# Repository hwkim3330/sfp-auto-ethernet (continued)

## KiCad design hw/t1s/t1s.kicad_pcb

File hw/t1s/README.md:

# T1S SFP: 10BASE-T1S

No 10BASE-T1S PHY speaks SGMII (they are all MII/RMII or SPI MAC-PHYs; see [../../docs/PARTS.md](../../docs/PARTS.md)).
So an FPGA sits between the two:
- the host's SGMII on a hard transceiver lane;
- our own PCS, ×100 rate adaptation, frame FIFOs and half-duplex MAC in fabric ([gw/](gw/));
- MII to a Microchip LAN8670.

**This is the board with the most unverified pieces.** See [What is not verified](#what-is-not-verified).

Schematic, 6-layer PCB (routed), fab outputs and a JLC panel are in place; the order sheet is [ORDER.md](ORDER.md). Nothing has been built.

**Re-laid 2026-10-08 on the corrected SFP edge** (SFF-8419 figure 7-2; until then the fingers were drawn mirrored, which would have put VccT on a ground contact). Do not order before the Gowin transceiver IP, synthesis and timing exist (below).

| Top | Bottom |
|---|---|
|  |  |

## Status

| | Result | How it was checked |
|---|---|---|
| Schematic | **ERC 0 errors** ([erc.rpt](erc.rpt)); 2 warnings, both "symbol differs from the library copy" (the two LDOs) | eeschema's own ERC (`run_erc.sh`) |
| Placement | 92 parts, no overlaps; housing height limits met | `make_t1s.py` |
| SFP edge | **all 20 fingers where SFF-8419 figure 7-2 puts them, with the right nets** | `tools/compliance.py` (positions written out independently of the generator) |
| Routing | **DRC 0 violations, 0 unconnected** ([drc.rpt](drc.rpt)) | hand-laid pairs, escapes and In2 buses, Freerouting 1.9.0 for the rest ([t1s.ses](t1s.ses), rebuilt with `--reuse-ses`), then KiCad DRC |
| KiCad 9 | **DRC 0 errors, 0 unconnected, schematic parity clean, ERC 0 errors** ([kicad9-drc.rpt](kicad9-drc.rpt), [kicad9-erc.rpt](kicad9-erc.rpt)) | `sh ../check_kicad9.sh t1s`. Only warnings are "differs from the library copy" |
| Fab | Gerbers + drill ([fab/t1s-gerbers.zip](fab/t1s-gerbers.zip)), [BOM](fab/t1s-bom.csv), [CPL](fab/t1s-cpl.csv), [1:1 print](fab/t1s-1to1.pdf) | `export_t1s.py` |
| Panel | 5 boards, 70.1 × 81.1 mm, **DRC 0 errors, 0 unconnected** with the board's rules ([jlc/panel-drc.rpt](jlc/panel-drc.rpt)) | `panel_t1s.py` (KiKit) |
| Gateware | `tb_bridge`, `tb_top` pass (`tb_top` with both lanes straight; an RX-inverting instance must fail) | Icarus Verilog, CI |
| Firmware | builds, 0 warnings | `make VARIANT=t1s`, CI |

## Parts

| | Part | LCSC | Why |
|---|---|---|---|
| FPGA | Gowin **GW5AT-LV15MG132C1/I0** | C54067362 | The only FPGA with real transceivers that fits the width (8 × 8 mm) and is in JLC stock |
| PHY | Microchip **LAN8670C2-E/LMX** | C20901523 | MII + PLCA, 5 × 5 VQFN (B1/C1 variants have no stock) |
| Reference | YXC OB2EL89CLIB112YLC-125M, 125 MHz LVDS 3225 | C7425465 | As the Gowin kit: LVDS, AC coupled at the FPGA |
| Configuration | GD25Q128EWIGR, 128 Mbit SPI NOR, WSON-8 6 × 5 | C2982923 | 128 Mbit so Gowin's default golden (retry) address 0x800000 is inside the part: main image at 0x000000, golden at 0x800000 |
| Core 0.946 V | TPS62822 buck | C473385 | Same circuit as the RJ45 board (57.6k / 100k) |
| 1.8 V, 1.2 V | TLV75518 / TLV75512, SOT-23-5 | C2877863 / C2877864 | VDDHAQ0; VDD12M + VCCLDO |
| MDI | ACT1210E-241 CMC, 2 × 100 nF 100 V, 49.9 Ω end-node termination | C6114822 … | Microchip AN1718 "BIN" |
| Connector | JST PH S2B-PH-K-S, 2 pins, right angle | C173752 | Wire to board, outside the cage |
| MCU | STM32G031F6P6 | C529333 | As the other boards: EEPROM, PHY bridge, TX_DISABLE / RX_LOS |

## Board

- 58.4 × 11.8 mm. The JST housing sits entirely past the cage front (44.3 mm).
- **Six layers:**

  | Layer | Use |
  |---|---|
  | F | FPGA balls, SGMII RX and the reference clock, MII, the beads, the MDI network, JTAG pads |
  | In1 | GND |
  | In2 | signals: the long buses (below), the ball field's escapes |
  | In3 | +3V3 plane |
  | In4 | GND, with the 0.95 V core as an island under the FPGA and the buck |
  | B | the TX pair, decaps, load switch, flash, buck, PHY straps, MCU, LDOs, test pads |

- **Why six:** 0.5 mm ball pitch leaves no room for a track between balls. So every used ball inside the outer ring has a **via in its pad** (0.25 / 0.15 mm in Gowin's 0.25 mm land, UG983 figure 4-8; filled and capped), and five supply rails sit interleaved around the ring. On six layers JLC fills and caps via-in-pad at no extra charge, and +3V3 and the core rail become planes the router doesn't have to route.
- **The core island is on In4, not In2.** On In2 it covered the ball field, so the small rails (VDDHAQ, V1P2) and the inner-ring signals had no way out. Under B only the field's stubs and decaps sit on it; the TX pair crosses it only on its last 0.75 mm into the balls.
- **Two In2 buses, laid by hand** (`IN2_BUS` in `make_t1s.py`; the long runs were found once by a maze search over the board before its dogbones went in, the west ends re-laid by hand in 2026-10). The slow fingers underneath read RX_LOS, SCL | SDA, TX_DISABLE, TX_FAULT from top to bottom, and the buses keep that order, so nothing crosses:
  - along the north edge, RX_LOS and SCL from the fingers to MCU pins 3 and 1;
  - along the south edge, from the ball field and the fingers to the MCU's bottom row, one lane each, stacked in the order the pins take them: V1P2 (to its LDO), RECONFIG_N, DONE, SDA above the pins' via row, FPGA_LINK, TX_DISABLE and TX_FAULT below it;
  - VDDHAQ leaves the ball field through row C and runs under the MCU to its LDO; MISO crosses over the flash.
  The MCU's pins follow the buses: I²C1 on PB8 (SCL, pin 1) and PA10 (SDA, pin 17, PA12's pad remapped), RX_LOS on PC15, TX_FAULT on PA4, TX_DISABLE on PA6 (`fw`, `VARIANT_T1S`).
- **Around the ball field:** JTAG leaves west on In2 to four pads on top beside the FPGA; the flash is turned 180° so CLK and MOSI reach it underneath; CRS, RXD0 and TXEN reach their straps through vias in the PHY's pads.
- **Configuration pins, from Gowin's pinout and UG720** (see [../../docs/REFERENCES.md](../../docs/REFERENCES.md)): CLKHOLD_N (K3) is pulled down during configuration and would hold the flash clock, so it is tied to +3V3; P1 doubles as SSPI_CS_N and is pulled up (R26) so the FPGA cannot select slave SPI after loading; MODE0 (N2) and MODE1 (N1) share one 4.7 kΩ pull-up (R1) for MSPI.
- **MDI network as AN1718 Rev D:** 100 nF 100 V series caps, 2 × 49.9 Ω end-node termination (0.75 W 1206, the closest stocked to AN1718's 1 W), 100 nF 100 V ‖ 100 kΩ to ground, ACT1210E-241 CMC; no copper under the CMC on any layer and no ground flood round the network on top.
- **SGMII pairs** (0.114 / 0.152 mm, coupled; [lengths.txt](lengths.txt)):
  - The fingers put TD (host → module) at the bottom of the tab and RD at the top, while all of lane 0's balls sit at the FPGA's top-left corner.
  - RX on F over In1: from its caps east, north up the ball field's west side (west of the JTAG pads), east above row A and down into A1 / A2. 13.8 / 13.0 mm, no vias.
  - TX on B over In4: out of B3 / C3's via-in-pads with 0.1 mm necks between the neighbouring ball vias, west to two vias by the RD caps, then on top to the caps. 8.5 / 8.0 mm, 2 / 2 vias, GND vias beside them.
- **Polarity: both lanes P to P, nothing inverted.** RX keeps its order by the way it turns. On TX, RD+ (pin 13) sits below RD− (pin 12), so the order has to turn over once: P stops at its via and M runs on underneath it to a via 1.2 mm further west; on top P's line then passes under M's via to the lower cap. No pair crosses itself. (Until 2026-10 the mirrored edge left RX inverted and the gateware undid it with `RX_INVERT`.) The reference clock is laid inverted so its two lines to the oscillator don't cross; for a clock that changes nothing.
- **LAN8670 land:** KiCad's VQFN-32 5 × 5 with a 3.5 × 3.5 exposed pad, the centre pad of Microchip's recommended land (package C04-500; EP 3.4 nominal). Symbol pin names follow DS60001573K (INH and GPIO0 left open, WAKE_IN on GND, as the datasheet says for unused pins).

## Regenerating

```bash
python3 make_t1s.py            # symbols, footprints, schematic, placed PCB
python3 make_t1s.py --route    # planes, dogbones, Freerouting, pours, repairs, DRC -> drc.rpt
sh ../check_kicad9.sh t1s      # the same board in KiCad 9
python3 export_t1s.py          # gerbers (6 copper layers), BOM, CPL, previews, 1:1 PDF
python3 panel_t1s.py           # 5-board panel + JLC files -> jlc/
```

## What is not verified

- **Hardware:** nothing has been built.
- **Gowin toolchain:**
  - The transceiver is Gowin's *Customized PHY* IP. It is generated in Gowin EDA with the settings in `gw/serdes_lane.v`, plus a small shim of ports. Neither exists yet.
  - Synthesis and timing have not been run.
- **Refclk choice:** 125 MHz for 1.25 Gb/s is the usual choice, but it has not been checked in Gowin's IP generator.
- **MIPI rails:** Gowin does not say whether they may stay unpowered, so they are powered (VDD12M 1.2 V, VDDAM on the core rail, VDDXM on 3.3 V).
- **Firmware** (`fw/`, `VARIANT=t1s`) builds but has never run: FPGA DONE / RECONFIG_N handling, the LAN8670's AN1699 set-up and PLCA over MDIO, RX_LOS from `FPGA_LINK` ([../../fw/README.md](../../fw/README.md)).
- **MDI polarity:** the pair leaves the PHY swapped (pins 30/31) so it does not cross itself on the way to its caps. 10BASE-T1S is DME coded, which is polarity-insensitive; check it on a real segment.
- **Fab limits:**
  - via-in-pad 0.15 mm drill, 0.25 mm pad (74 of them: the ball field, a few PHY pads);
  - 0.1 mm lines between ball vias;
  - 0.2 mm hole-to-copper.

  Confirm all three against JLC's 6-layer DFM before ordering.

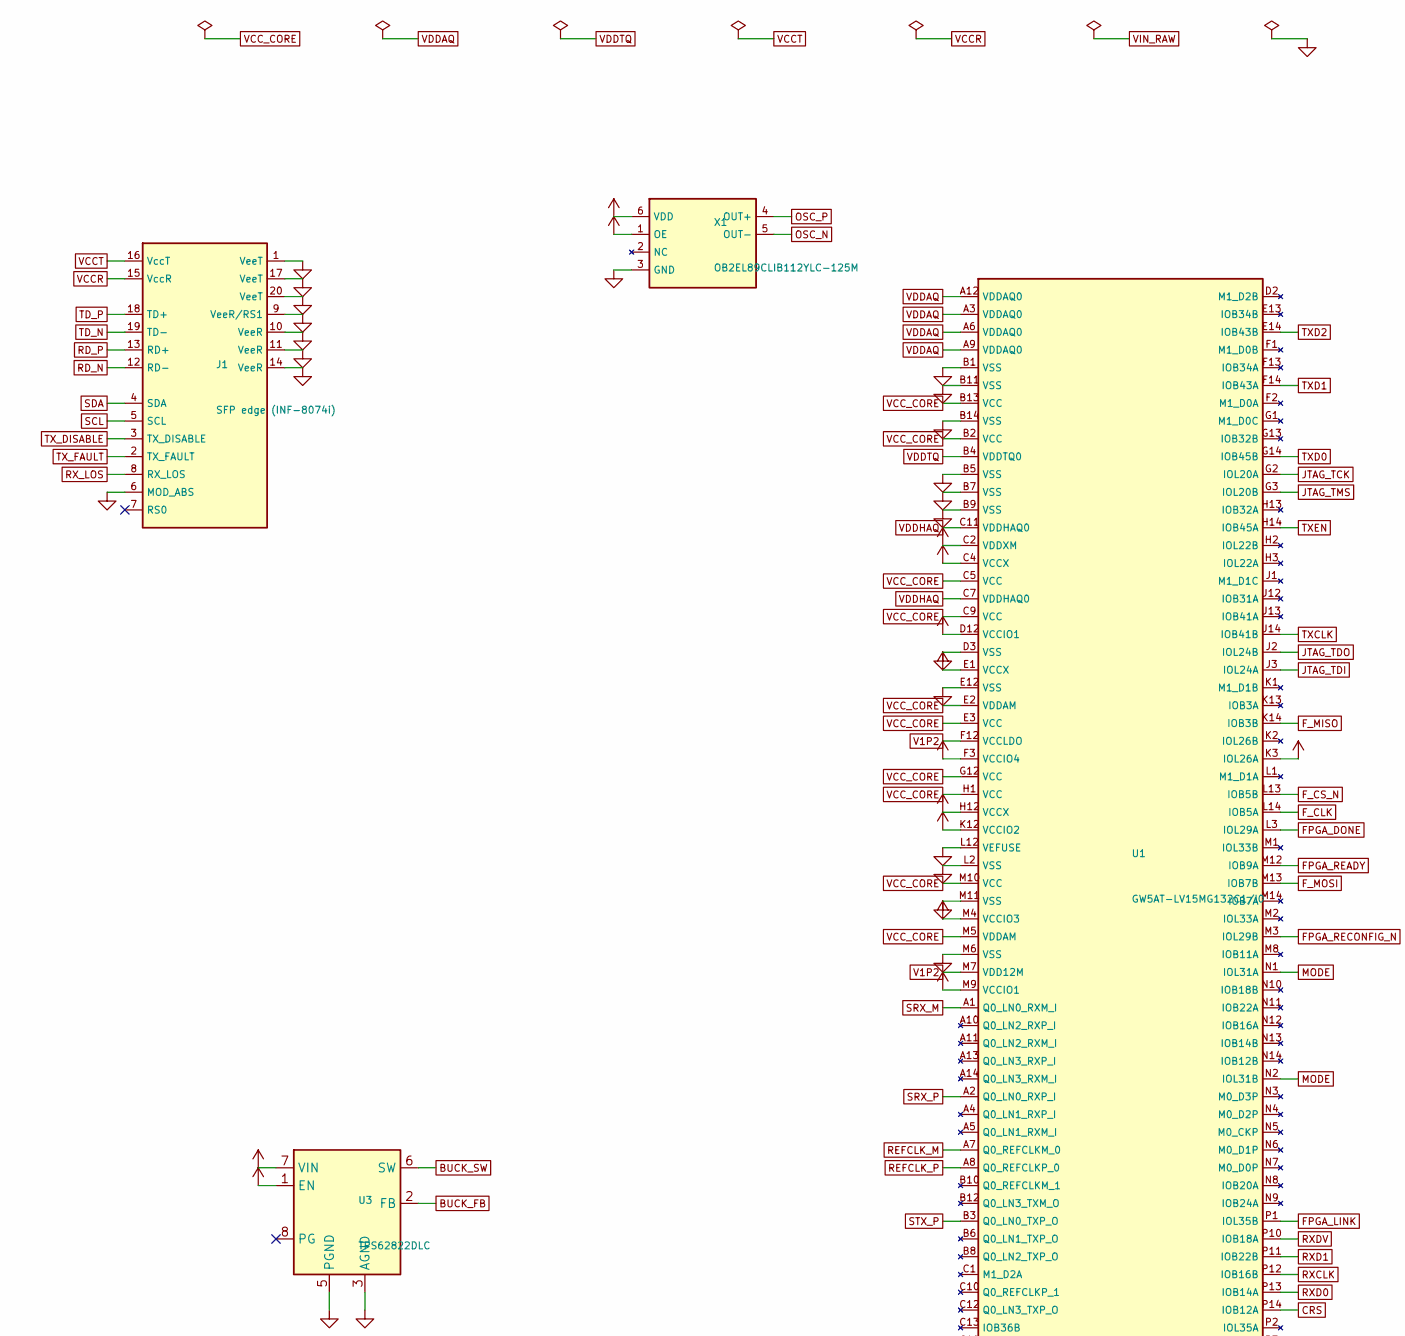
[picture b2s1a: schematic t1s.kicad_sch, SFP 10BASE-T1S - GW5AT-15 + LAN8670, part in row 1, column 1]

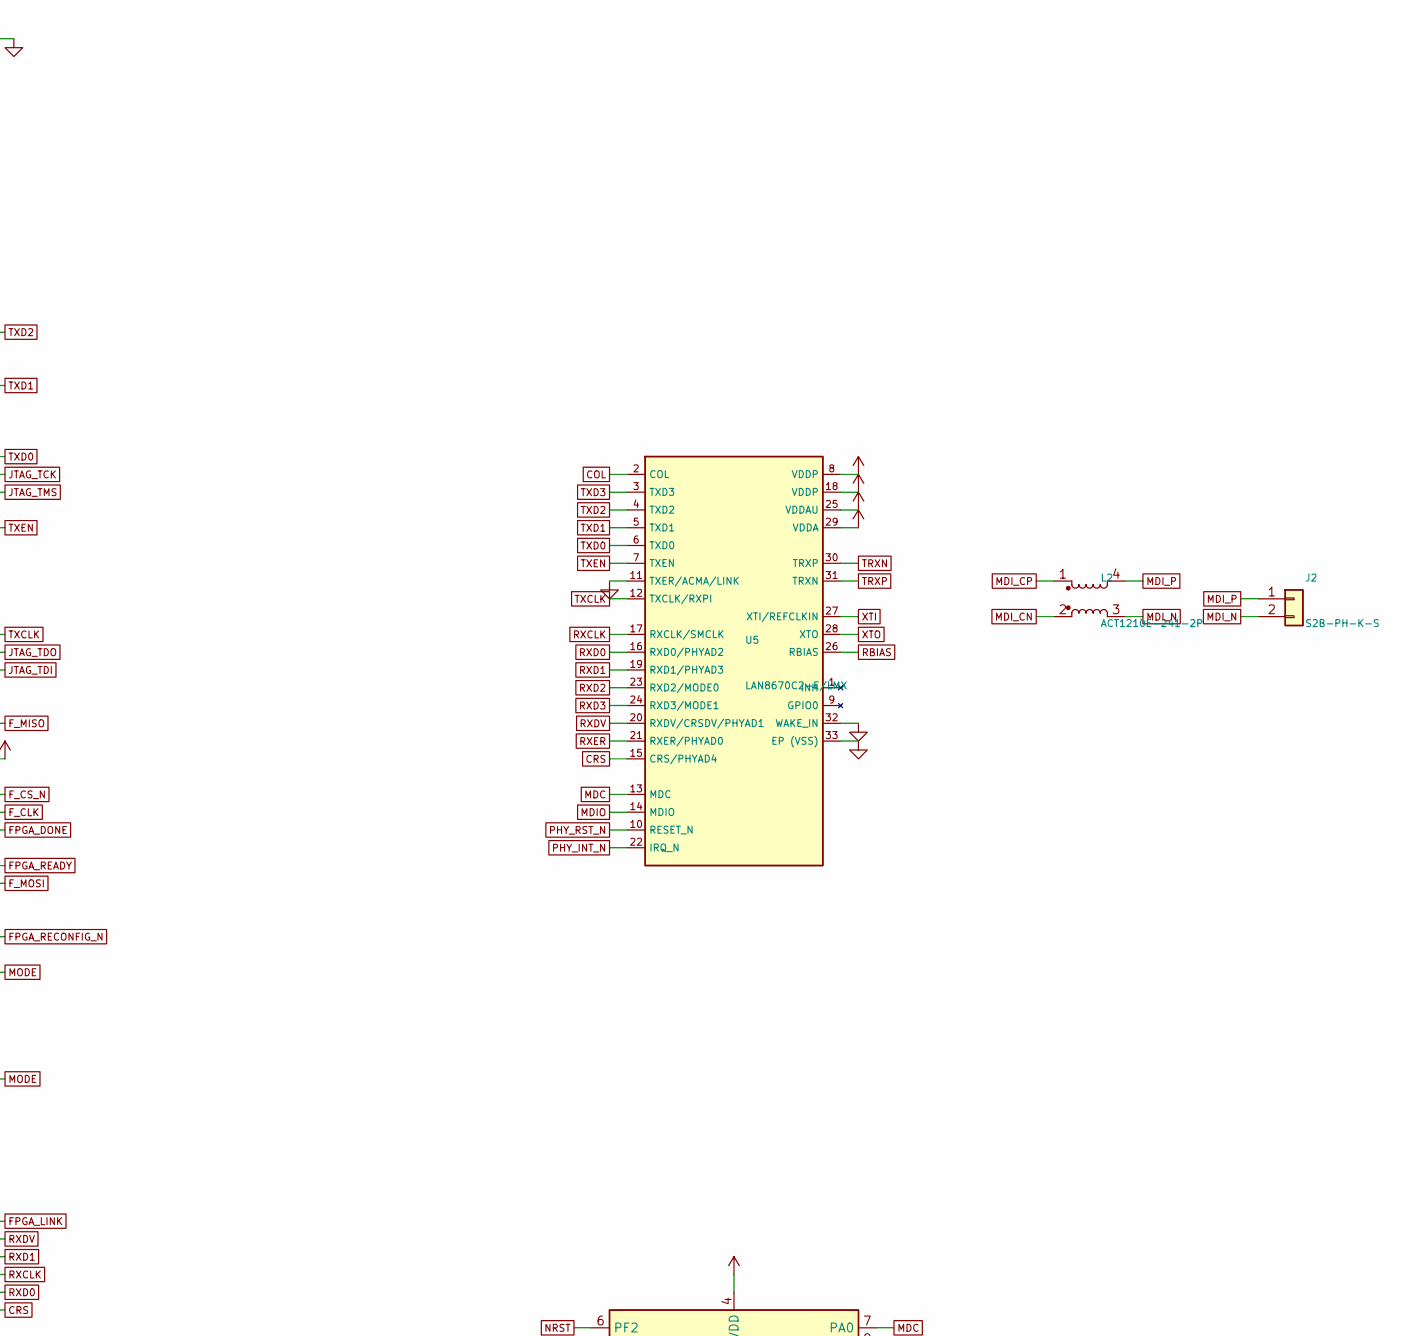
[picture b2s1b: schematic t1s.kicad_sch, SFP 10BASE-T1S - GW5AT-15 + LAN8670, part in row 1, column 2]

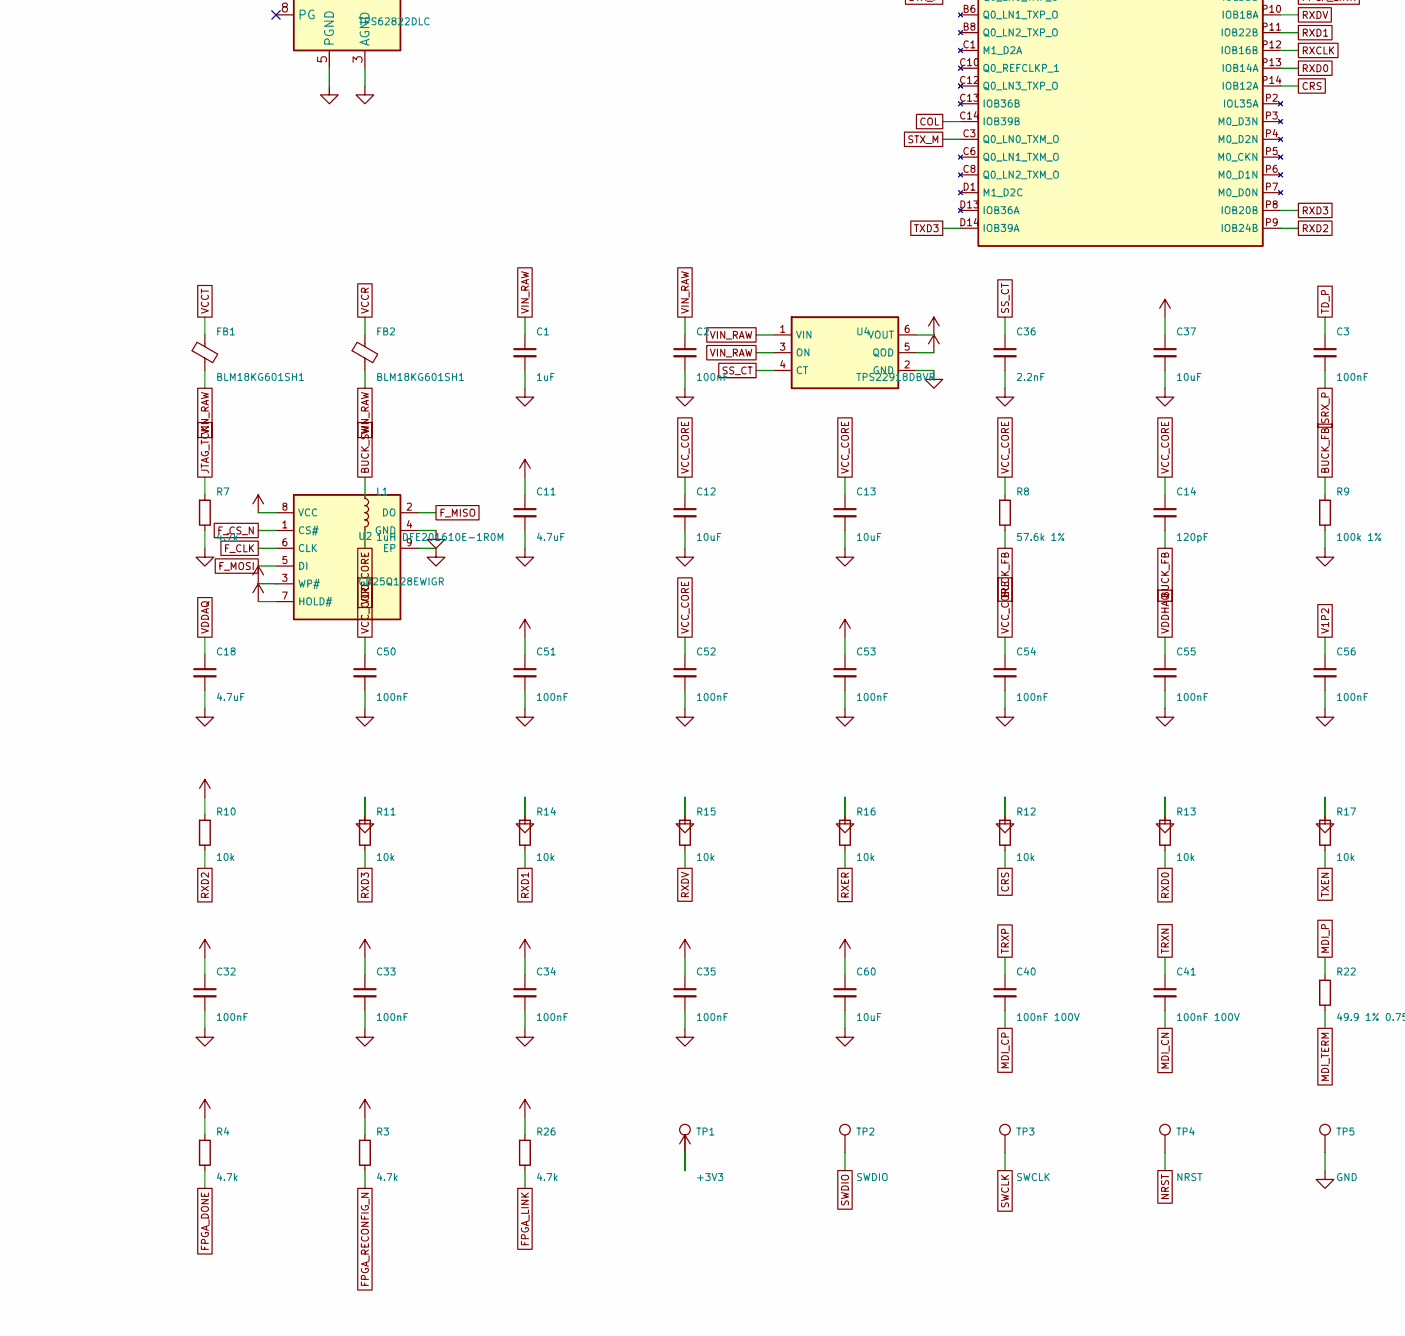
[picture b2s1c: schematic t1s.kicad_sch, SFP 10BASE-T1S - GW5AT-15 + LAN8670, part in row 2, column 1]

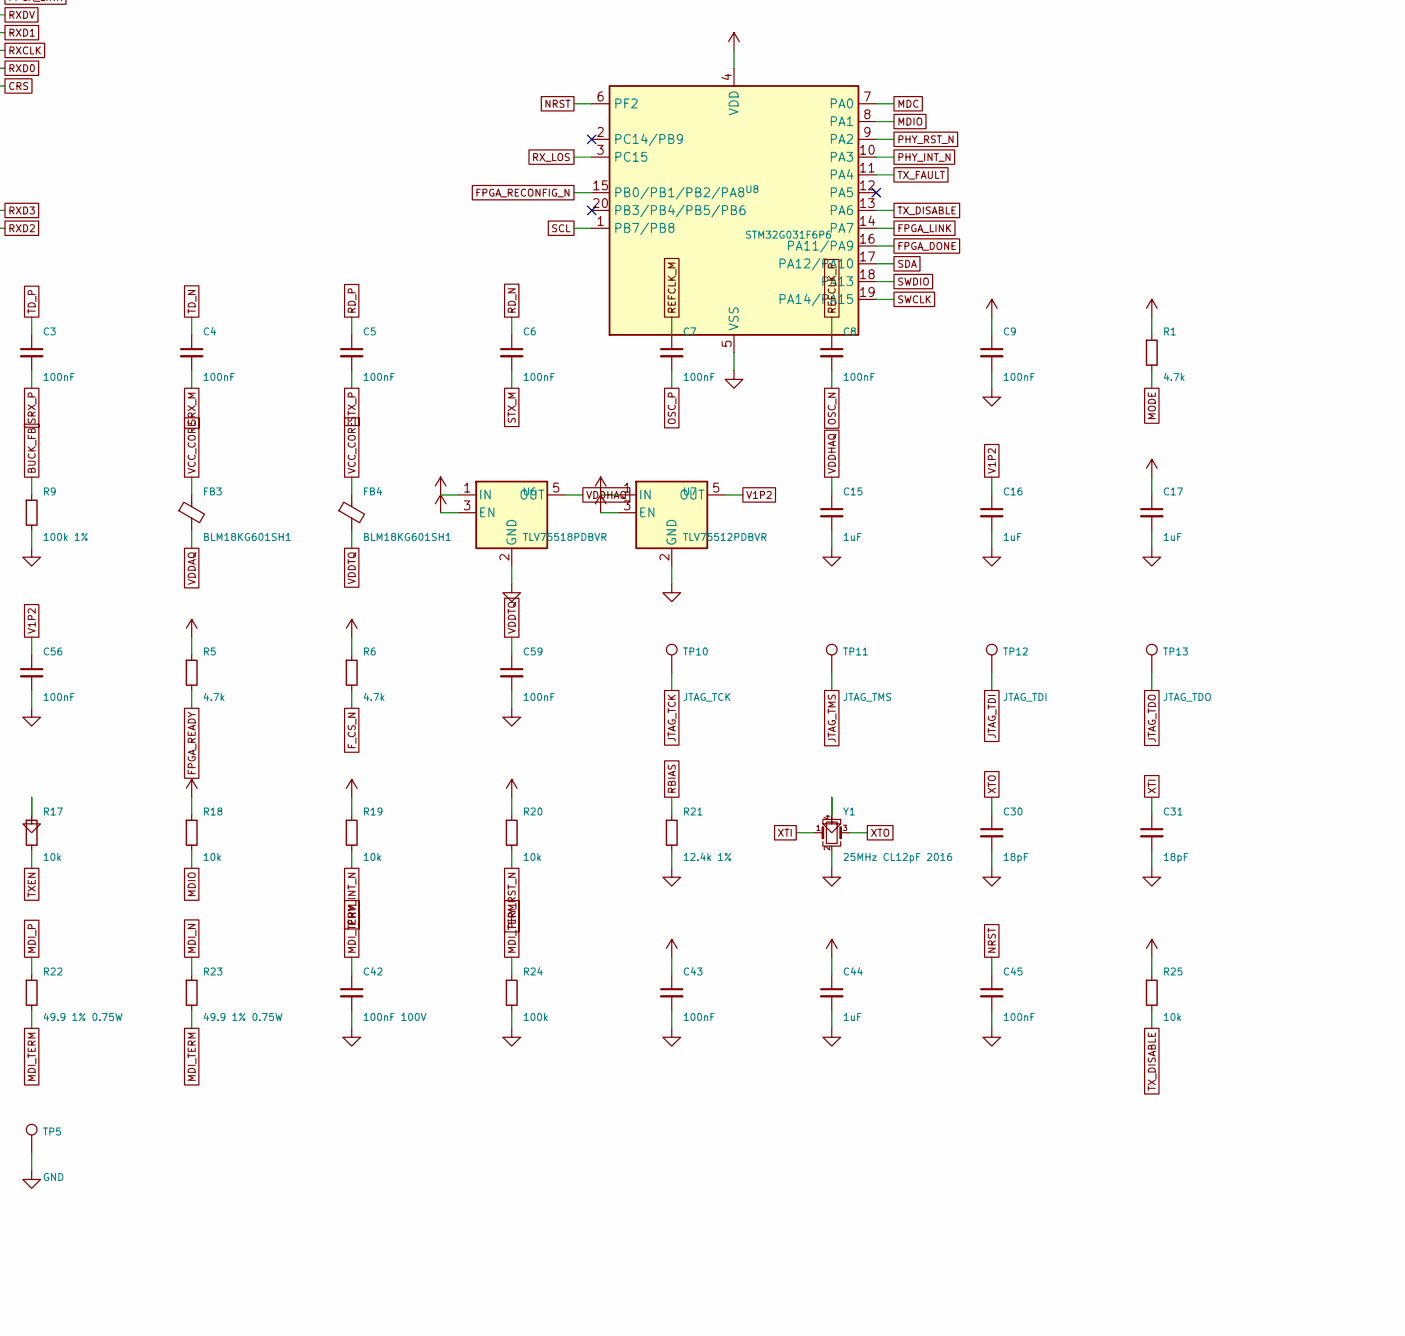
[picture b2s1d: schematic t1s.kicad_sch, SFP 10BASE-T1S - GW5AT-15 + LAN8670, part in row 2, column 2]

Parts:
C1, C15, C16, C17, C44: 1uF; C_0402_1005Metric; LCSC C52923
C2, C43, C45: 100nF; C_0402_1005Metric; LCSC C1525
C3, C4, C5, C6, C7, C8, C9, C32, C33, C34, C35, C50, C51, C52, C53, C54, C55, C56, C59: 100nF; C_0201_0603Metric; LCSC C76928
C11, C18: 4.7uF; C_0402_1005Metric; LCSC C23733
C12, C13, C60: 10uF; C_0603_1608Metric; LCSC C19702
C14: 120pF; C_0201_0603Metric; LCSC C161406
C30, C31: 18pF; C_0201_0603Metric; LCSC C62164
C36: 2.2nF; C_0402_1005Metric; LCSC C106861
C37: 10uF; C_0402_1005Metric; LCSC C15525
C40, C41, C42: 100nF 100V; C_0805_2012Metric; LCSC C28233
FB1, FB2, FB3, FB4: BLM18KG601SH1; L_0603_1608Metric; MPN BLM18KG601SH1; LCSC C710379
J1: SFP edge (INF-8074i); SFP_Module_Edge
J2: S2B-PH-K-S; JST_PH_S2B-PH-K_1x02_P2.00mm_Horizontal; MPN S2B-PH-K-S(LF)(SN); LCSC C173752
L1: 1uH DFE201610E-1R0M; L_Murata_DFE201610P; MPN DFE201610E-1R0M; LCSC C161082
L2: ACT1210E-241-2P; L_CommonMode_3225; MPN ACT1210E-241-2P-TL00; LCSC C6114822
R1, R3, R4, R5, R6, R7, R26: 4.7k; R_0201_0603Metric; LCSC C142008
R8: 57.6k 1%; R_0201_0603Metric; LCSC C423476
R9: 100k 1%; R_0201_0603Metric; LCSC C106224
R10, R11, R12, R13, R14, R15, R16, R17, R18, R19, R20, R25: 10k; R_0201_0603Metric; LCSC C106225
R21: 12.4k 1%; R_0402_1005Metric; LCSC C284314
R22, R23: 49.9 1% 0.75W; R_1206_3216Metric; MPN CRCW120649R9FKEAHP; LCSC C4014562
R24: 100k; R_0805_2012Metric; LCSC C118847
TP1: +3V3; TestPoint_Pad_D1.0mm
TP2: SWDIO; TestPoint_Pad_D1.0mm
TP3: SWCLK; TestPoint_Pad_D1.0mm
TP4: NRST; TestPoint_Pad_D1.0mm
TP5: GND; TestPoint_Pad_D1.0mm
TP10: JTAG_TCK; TestPoint_Pad_D1.0mm_NoSilk
TP11: JTAG_TMS; TestPoint_Pad_D1.0mm_NoSilk
TP12: JTAG_TDI; TestPoint_Pad_D1.0mm_NoSilk
TP13: JTAG_TDO; TestPoint_Pad_D1.0mm_NoSilk
U1: GW5AT-LV15MG132C1/I0; Gowin_MBGA-132_8x8mm_P0.5mm; MPN GW5AT-LV15MG132C1/I0; LCSC C54067362
U2: GD25Q128EWIGR; WSON-8-1EP_6x5mm_P1.27mm_EP3.4x4.3mm; MPN GD25Q128EWIGR; LCSC C2982923
U3: TPS62822DLC; Texas_VSON-HR-8_1.5x2mm_P0.5mm; MPN TPS62822DLCR; LCSC C473385
U4: TPS22918DBVR; SOT-23-6; MPN TPS22918DBVR; LCSC C131941
U5: LAN8670C2-E/LMX; VQFN-32-1EP_5x5mm_P0.5mm_EP3.5x3.5mm; MPN LAN8670C2-E/LMX; LCSC C20901523
U6: TLV75518PDBVR; SOT-23-5; MPN TLV75518PDBVR; LCSC C2877863
U7: TLV75512PDBVR; SOT-23-5; MPN TLV75512PDBVR; LCSC C2877864
U8: STM32G031F6P6; TSSOP-20_4.4x6.5mm_P0.65mm; MPN STM32G031F6P6; LCSC C529333
X1: OB2EL89CLIB112YLC-125M; Oscillator_YXC_3225-6Pin_LVDS; MPN OB2EL89CLIB112YLC-125M; LCSC C7425465
Y1: 25MHz CL12pF 2016; Crystal_SMD_2016-4Pin_2.0x1.6mm; LCSC C5210656

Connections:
+3V3: C9.1, C11.1, C17.1, C32.1, C33.1, C34.1, C35.1, C37.1, C43.1, C44.1, C51.1, C53.1, C60.1, R1.1, R3.1, R4.1, R5.1, R6.1, R10.1, R18.1, R19.1, R20.1, R25.1, R26.1, TP1.1, U1.C2 (VDDXM), U1.C4 (VCCX), U1.D12 (VCCIO1), U1.E1 (VCCX), U1.F3 (VCCIO4), U1.H12 (VCCX), U1.K3 (IOL26A), U1.K12 (VCCIO2), U1.M4 (VCCIO3), U1.M9 (VCCIO1), U2.3 (WP#), U2.7 (HOLD#), U2.8 (VCC), U3.1 (EN), U3.7 (VIN), U4.5 (QOD), U4.6 (VOUT), U5.8 (VDDP), U5.18 (VDDP), U5.25 (VDDAU), U5.29 (VDDA), U6.1 (IN), U6.3 (EN), U7.1 (IN), U7.3 (EN), U8.4 (VDD), X1.1 (OE), X1.6 (VDD)
BUCK_FB: C14.2, R8.2, R9.1, U3.2 (FB)
BUCK_SW: L1.1, U3.6 (SW)
COL: U1.C14 (IOB39B), U5.2 (COL)
CRS: R12.2, U1.P14 (IOB12A), U5.15 (CRS/PHYAD4)
FPGA_DONE: R4.2, U1.L3 (IOL29A), U8.16 (PA11/PA9)
FPGA_LINK: R26.2, U1.P1 (IOL35B), U8.14 (PA7)
FPGA_READY: R5.2, U1.M12 (IOB9A)
FPGA_RECONFIG_N: R3.2, U1.M3 (IOL29B), U8.15 (PB0/PB1/PB2/PA8)
F_CLK: U1.L14 (IOB5A), U2.6 (CLK)
F_CS_N: R6.2, U1.L13 (IOB5B), U2.1 (CS#)
F_MISO: U1.K14 (IOB3B), U2.2 (DO)
F_MOSI: U1.M13 (IOB7B), U2.5 (DI)
GND: C1.2, C2.2, C9.2, C11.2, C12.2, C13.2, C15.2, C16.2, C17.2, C18.2, C30.2, C31.2, C32.2, C33.2, C34.2, C35.2, C36.2, C37.2, C42.2, C43.2, C44.2, C45.2, C50.2, C51.2, C52.2, C53.2, C54.2, C55.2, C56.2, C59.2, C60.2, J1.1 (VeeT), J1.6 (MOD_ABS), J1.9 (VeeR/RS1), J1.10 (VeeR), J1.11 (VeeR), J1.14 (VeeR), J1.17 (VeeT), J1.20 (VeeT), R7.2, R9.2, R11.1, R12.1, R13.1, R14.1, R15.1, R16.1, R17.1, R21.2, R24.2, TP5.1, U1.B1 (VSS), U1.B5 (VSS), U1.B7 (VSS), U1.B9 (VSS), U1.B11 (VSS), U1.B14 (VSS), U1.D3 (VSS), U1.E12 (VSS), U1.L2 (VSS), U1.L12 (VEFUSE), U1.M6 (VSS), U1.M11 (VSS), U2.4 (GND), U2.9 (EP), U3.3 (AGND), U3.5 (PGND), U4.2 (GND), U5.11 (TXER/ACMA/LINK), U5.32 (WAKE_IN), U5.33 (EP (VSS)), U6.2 (GND), U7.2 (GND), U8.5 (VSS), X1.3 (GND), Y1.2, Y1.4
JTAG_TCK: R7.1, TP10.1, U1.G2 (IOL20A)
JTAG_TDI: TP12.1, U1.J3 (IOL24A)
JTAG_TDO: TP13.1, U1.J2 (IOL24B)
JTAG_TMS: TP11.1, U1.G3 (IOL20B)
MDC: U5.13 (MDC), U8.7 (PA0)
MDIO: R18.2, U5.14 (MDIO), U8.8 (PA1)
MDI_CN: C41.2, L2.2
MDI_CP: C40.2, L2.1
MDI_N: J2.2, L2.3, R23.1
MDI_P: J2.1, L2.4, R22.1
MDI_TERM: C42.1, R22.2, R23.2, R24.1
MODE: R1.2, U1.N1 (IOL31A), U1.N2 (IOL31B)
NRST: C45.1, TP4.1, U8.6 (PF2)
OSC_N: C8.2, X1.5 (OUT-)
OSC_P: C7.2, X1.4 (OUT+)
PHY_INT_N: R19.2, U5.22 (IRQ_N), U8.10 (PA3)
PHY_RST_N: R20.2, U5.10 (RESET_N), U8.9 (PA2)
RBIAS: R21.1, U5.26 (RBIAS)
RD_N: C6.1, J1.12 (RD-)
RD_P: C5.1, J1.13 (RD+)
REFCLK_M: C7.1, U1.A7 (Q0_REFCLKM_0)
REFCLK_P: C8.1, U1.A8 (Q0_REFCLKP_0)
RXCLK: U1.P12 (IOB16B), U5.17 (RXCLK/SMCLK)
RXD0: R13.2, U1.P13 (IOB14A), U5.16 (RXD0/PHYAD2)
RXD1: R14.2, U1.P11 (IOB22B), U5.19 (RXD1/PHYAD3)
RXD2: R10.2, U1.P9 (IOB24B), U5.23 (RXD2/MODE0)
RXD3: R11.2, U1.P8 (IOB20B), U5.24 (RXD3/MODE1)
RXDV: R15.2, U1.P10 (IOB18A), U5.20 (RXDV/CRSDV/PHYAD1)
RXER: R16.2, U5.21 (RXER/PHYAD0)
RX_LOS: J1.8 (RX_LOS), U8.3 (PC15)
SCL: J1.5 (SCL), U8.1 (PB7/PB8)
SDA: J1.4 (SDA), U8.17 (PA12/PA10)
SRX_M: C4.2, U1.A1 (Q0_LN0_RXM_I)
SRX_P: C3.2, U1.A2 (Q0_LN0_RXP_I)
SS_CT: C36.1, U4.4 (CT)
STX_M: C6.2, U1.C3 (Q0_LN0_TXM_O)
STX_P: C5.2, U1.B3 (Q0_LN0_TXP_O)
SWCLK: TP3.1, U8.19 (PA14/PA15)
SWDIO: TP2.1, U8.18 (PA13)
TD_N: C4.1, J1.19 (TD-)
TD_P: C3.1, J1.18 (TD+)
TRXN: C41.1, U5.30 (TRXP)
TRXP: C40.1, U5.31 (TRXN)
TXCLK: U1.J14 (IOB41B), U5.12 (TXCLK/RXPI)
TXD0: U1.G14 (IOB45B), U5.6 (TXD0)
TXD1: U1.F14 (IOB43A), U5.5 (TXD1)
TXD2: U1.E14 (IOB43B), U5.4 (TXD2)
TXD3: U1.D14 (IOB39A), U5.3 (TXD3)
TXEN: R17.2, U1.H14 (IOB45A), U5.7 (TXEN)
TX_DISABLE: J1.3 (TX_DISABLE), R25.2, U8.13 (PA6)
TX_FAULT: J1.2 (TX_FAULT), U8.11 (PA4)
V1P2: C16.1, C56.1, U1.F12 (VCCLDO), U1.M7 (VDD12M), U7.5 (OUT)
VCCR: FB2.1, J1.15 (VccR)
VCCT: FB1.1, J1.16 (VccT)
VCC_CORE: C12.1, C13.1, C14.1, C50.1, C52.1, C54.1, FB3.1, FB4.1, L1.2, R8.1, U1.B2 (VCC), U1.B13 (VCC), U1.C5 (VCC), U1.C9 (VCC), U1.E2 (VDDAM), U1.E3 (VCC), U1.G12 (VCC), U1.H1 (VCC), U1.M5 (VDDAM), U1.M10 (VCC)
VDDAQ: C18.1, FB3.2, U1.A3 (VDDAQ0), U1.A6 (VDDAQ0), U1.A9 (VDDAQ0), U1.A12 (VDDAQ0)
VDDHAQ: C15.1, C55.1, U1.C7 (VDDHAQ0), U1.C11 (VDDHAQ0), U6.5 (OUT)
VDDTQ: C59.1, FB4.2, U1.B4 (VDDTQ0)
VIN_RAW: C1.1, C2.1, FB1.2, FB2.2, U4.1 (VIN), U4.3 (ON)
XTI: C31.1, U5.27 (XTI/REFCLKIN), Y1.1
XTO: C30.1, U5.28 (XTO), Y1.3

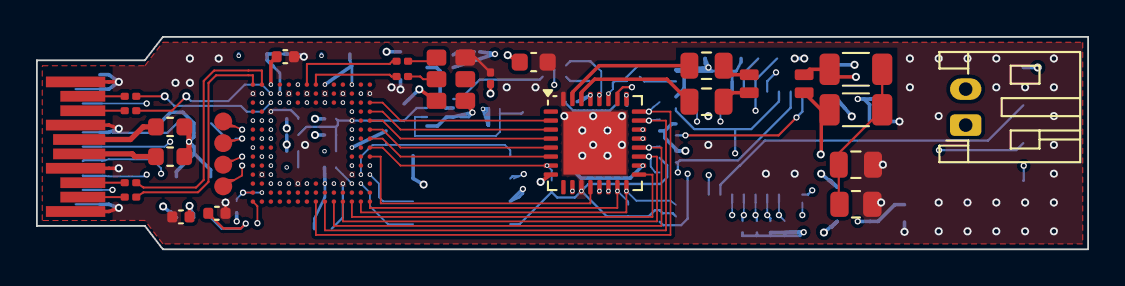
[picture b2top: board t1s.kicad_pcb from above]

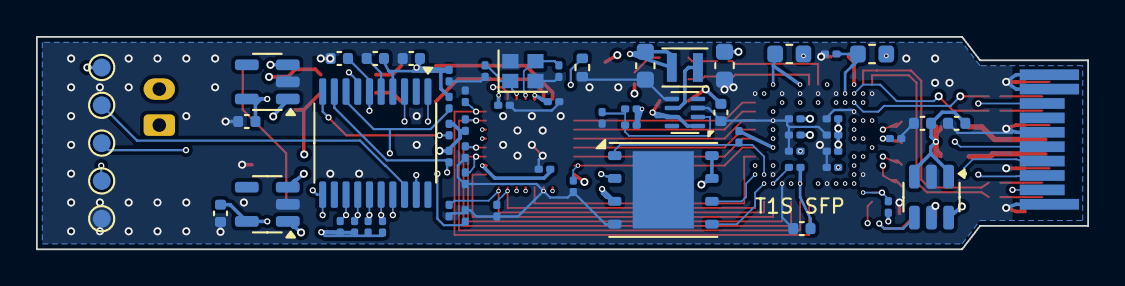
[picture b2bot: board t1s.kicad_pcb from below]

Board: 6 copper layers, 58.4 x 11.8 mm, 92 parts (63 on the bottom side), 75 nets.

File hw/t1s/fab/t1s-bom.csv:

Comment,Designator,Footprint,MPN,Qty,Fitted
1uF,"C1,C15,C16,C17,C44",C_0402_1005Metric,,5,yes
4.7uF,"C11,C18",C_0402_1005Metric,,2,yes
10uF,"C12,C13,C60",C_0603_1608Metric,,3,yes
120pF,C14,C_0201_0603Metric,,1,yes
100nF,"C2,C43,C45",C_0402_1005Metric,,3,yes
100nF,"C3,C4,C5,C6,C7,C8,C9,C50,C51,C52,C53,C54,C55,C56,C59,C32,C33,C34,C35",C_0201_0603Metric,,19,yes
18pF,"C30,C31",C_0201_0603Metric,,2,yes
2.2nF,C36,C_0402_1005Metric,,1,yes
10uF,C37,C_0402_1005Metric,,1,yes
100nF 100V,"C40,C41,C42",C_0805_2012Metric,,3,yes
BLM18KG601SH1,"FB1,FB2,FB3,FB4",L_0603_1608Metric,BLM18KG601SH1,4,yes
S2B-PH-K-S,J2,JST_PH_S2B-PH-K_1x02_P2.00mm_Horizontal,S2B-PH-K-S(LF)(SN),1,yes
1uH DFE201610E-1R0M,L1,L_Murata_DFE201610P,DFE201610E-1R0M,1,yes
ACT1210E-241-2P,L2,L_CommonMode_3225,ACT1210E-241-2P-TL00,1,yes
4.7k,"R1,R7,R5,R6,R4,R3,R26",R_0201_0603Metric,,7,yes
10k,"R10,R11,R14,R15,R16,R12,R13,R17,R18,R19,R20,R25",R_0201_0603Metric,,12,yes
12.4k 1%,R21,R_0402_1005Metric,,1,yes
49.9 1% 0.75W,"R22,R23",R_1206_3216Metric,CRCW120649R9FKEAHP,2,yes
100k,R24,R_0805_2012Metric,,1,yes
57.6k 1%,R8,R_0201_0603Metric,,1,yes
100k 1%,R9,R_0201_0603Metric,,1,yes
GW5AT-LV15MG132C1/I0,U1,Gowin_MBGA-132_8x8mm_P0.5mm,GW5AT-LV15MG132C1/I0,1,yes
GD25Q128EWIGR,U2,WSON-8-1EP_6x5mm_P1.27mm_EP3.4x4.3mm,GD25Q128EWIGR,1,yes
TPS62822DLC,U3,Texas_VSON-HR-8_1.5x2mm_P0.5mm,TPS62822DLCR,1,yes
TPS22918DBVR,U4,SOT-23-6,TPS22918DBVR,1,yes
LAN8670C2-E/LMX,U5,VQFN-32-1EP_5x5mm_P0.5mm_EP3.5x3.5mm,LAN8670C2-E/LMX,1,yes
TLV75518PDBVR,U6,SOT-23-5,TLV75518PDBVR,1,yes
TLV75512PDBVR,U7,SOT-23-5,TLV75512PDBVR,1,yes
STM32G031F6P6,U8,TSSOP-20_4.4x6.5mm_P0.65mm,STM32G031F6P6,1,yes
OB2EL89CLIB112YLC-125M,X1,Oscillator_YXC_3225-6Pin_LVDS,OB2EL89CLIB112YLC-125M,1,yes
25MHz CL12pF 2016,Y1,Crystal_SMD_2016-4Pin_2.0x1.6mm,,1,yes
